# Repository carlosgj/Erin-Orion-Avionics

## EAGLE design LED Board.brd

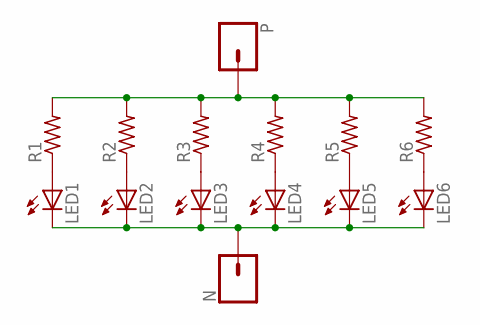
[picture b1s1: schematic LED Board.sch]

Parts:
LED1, LED2, LED3, LED4, LED5, LED6: LEDCHIPLED_1206; CHIPLED_1206
N: CONN_01; 1X01
P: CONN_01; 1X01
R1, R2, R3, R4, R5, R6: R-US_M1206; M1206

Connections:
unnamed: LED1.A, R1.1
unnamed: LED2.A, R2.1
unnamed: LED3.A, R3.1
unnamed: LED4.A, R4.1
unnamed: LED5.A, R5.1
unnamed: LED6.A, R6.1
unnamed: P.1, R1.2, R2.2, R3.2, R4.2, R5.2, R6.2
unnamed: LED1.C, LED2.C, LED3.C, LED4.C, LED5.C, LED6.C, N.1

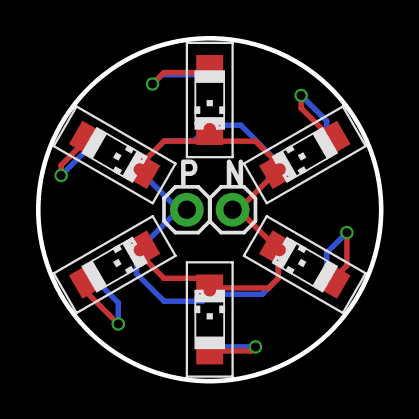
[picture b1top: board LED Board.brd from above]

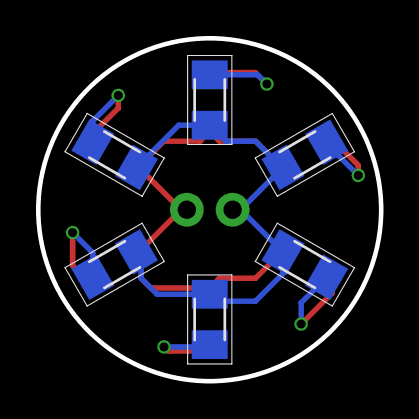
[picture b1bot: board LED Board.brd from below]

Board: 2 copper layers, 19.1 x 19.1 mm, 14 parts (6 on the bottom side), 8 nets.

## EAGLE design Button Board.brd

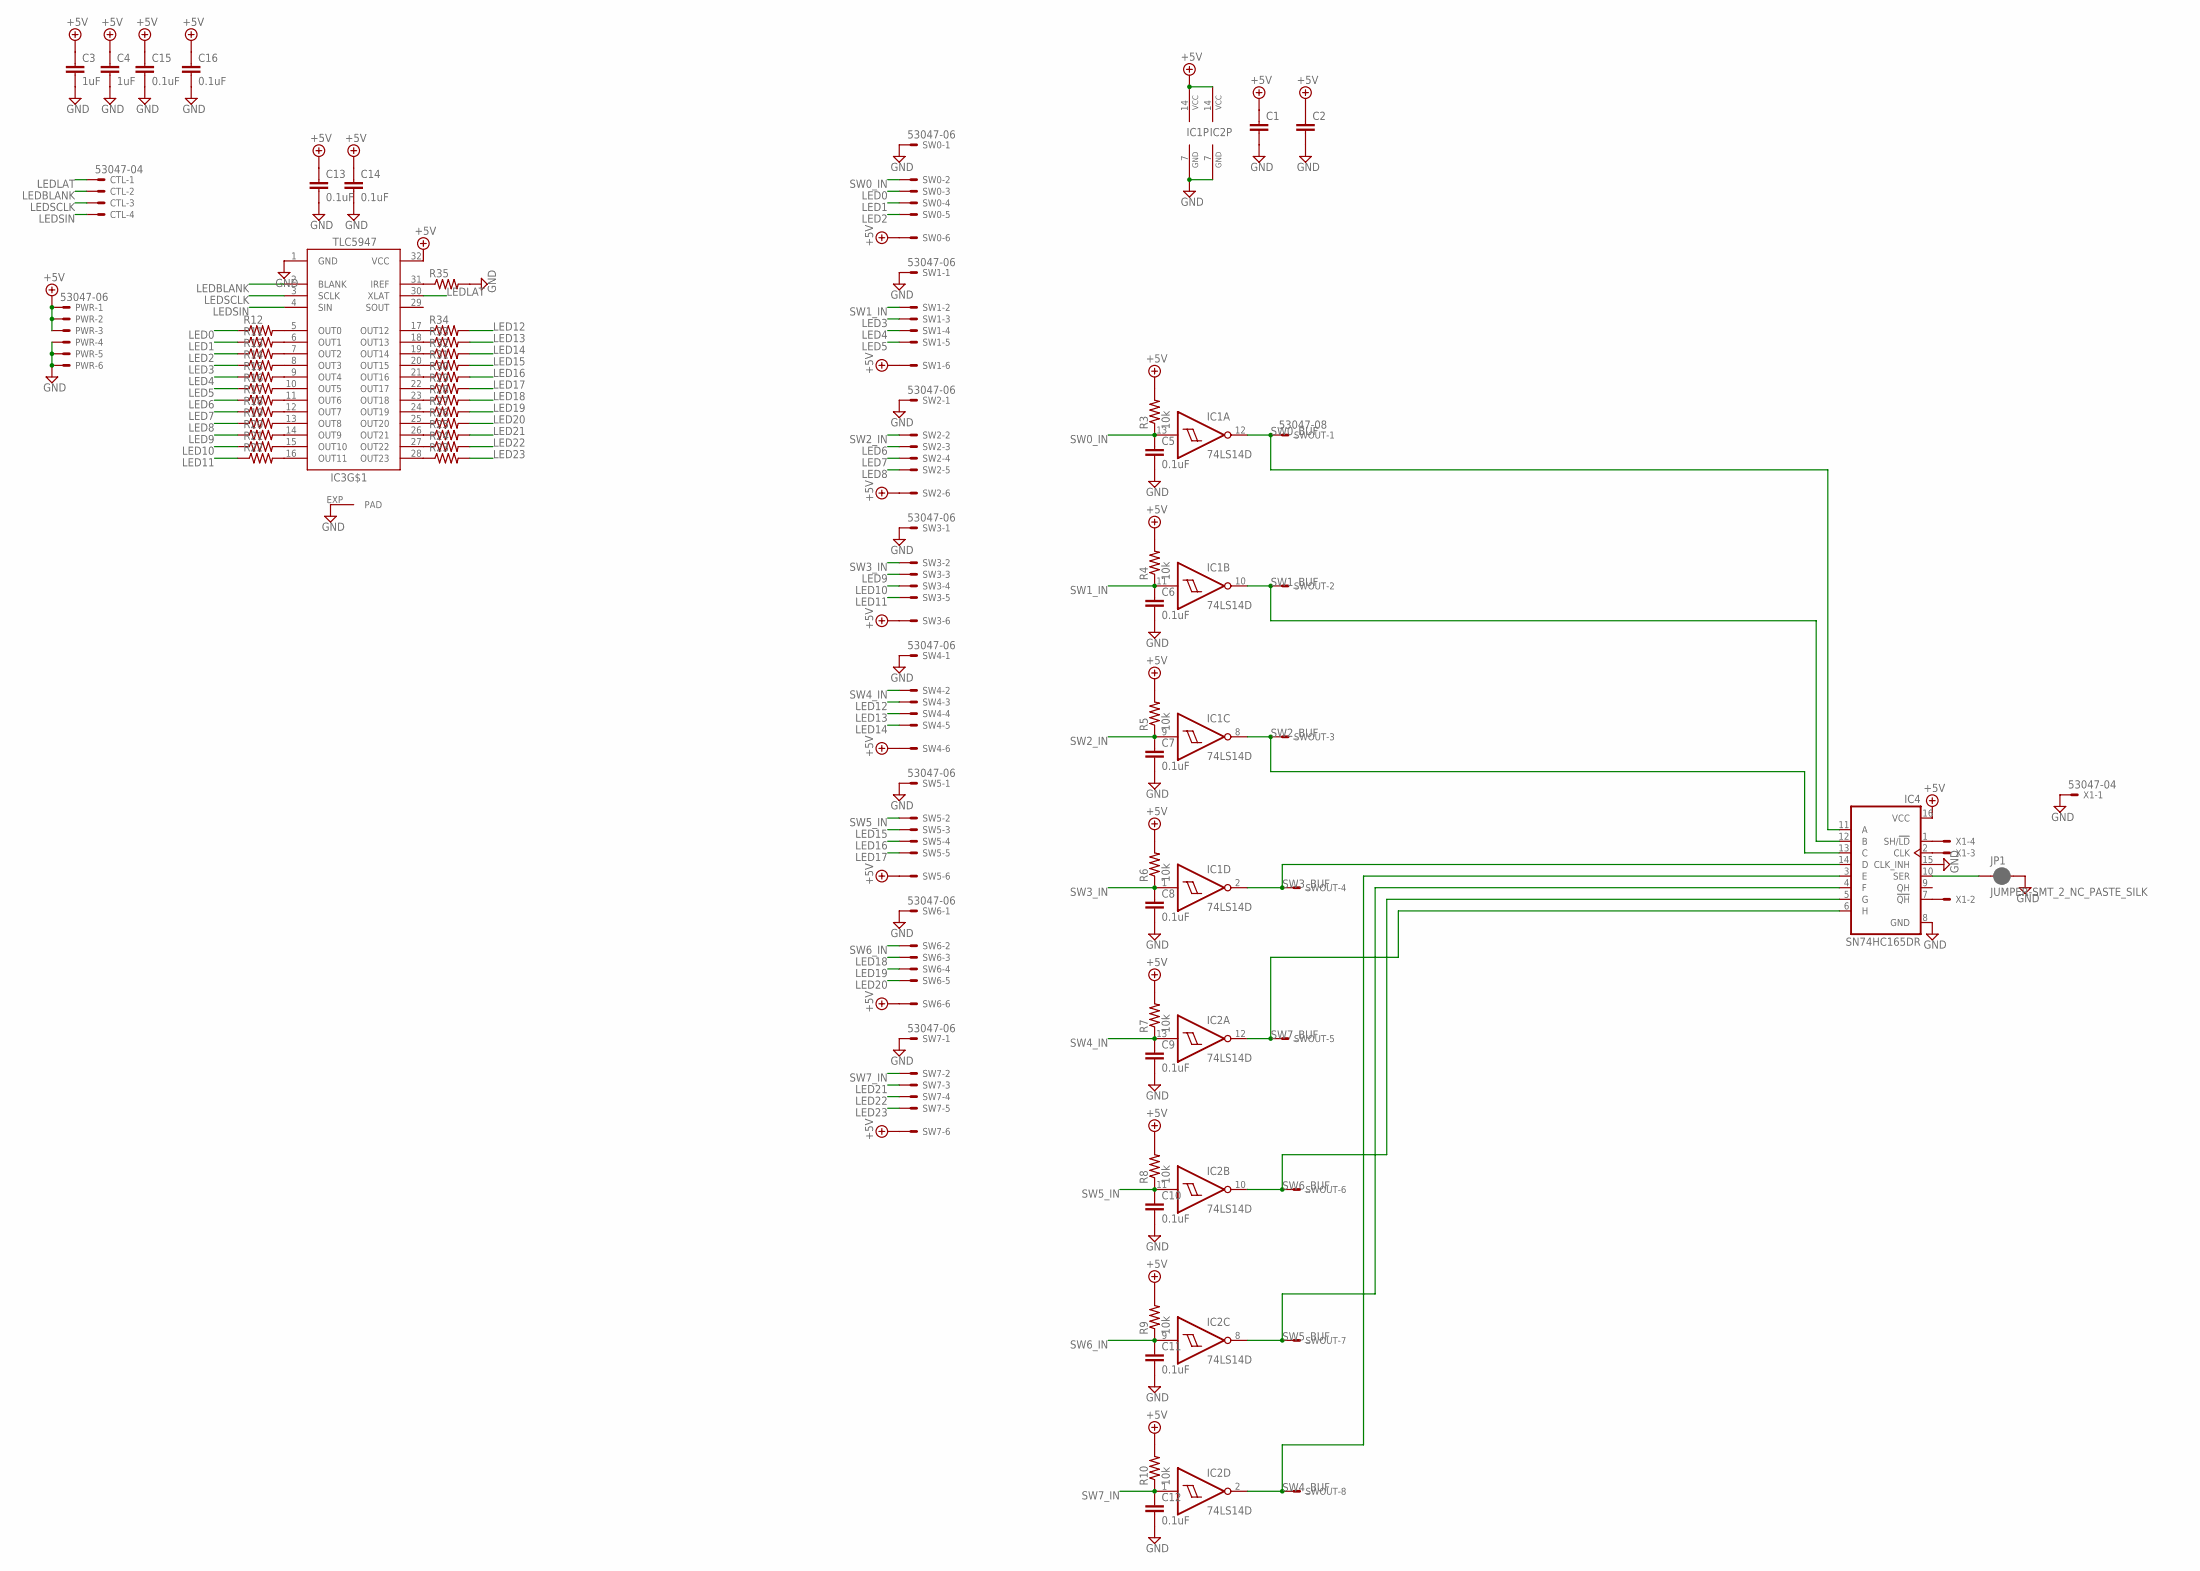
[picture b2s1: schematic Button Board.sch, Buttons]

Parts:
C1, C2: C-EUC1206; C1206
C3, C4: 1uF; C1206K
C5, C6, C7, C8, C9, C10, C11, C12, C13, C14: 0.1uF; C1206
C15, C16: 0.1uF; C1206K
CTL: 53047-04
IC1, IC2: 74LS14D; SO14
IC3: TLC5947-DAP; HTSSOP32DAP
IC4: SN74HC165DR; SO16
JP1: JUMPER-SMT_2_NC_PASTE_SILK; SMT-JUMPER_2_NC_PASTE_SILK
PWR: 53047-06
R3, R4, R5, R6, R7, R8, R9, R10: 10k; M1206
R11, R12, R13, R14, R15, R16, R17, R18, R19, R20, R21, R22, R23, R24, R25, R26, R27, R28, R29, R30, R31, R32, R33, R34, R35: R-US_M1206; M1206
SW0, SW1, SW2, SW3, SW4, SW5, SW6, SW7: 53047-06
SWOUT: 53047-08
X1: 53047-04

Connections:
+5V: C1.1, C2.1, C3.1, C4.1, C13.1, C14.1, C15.1, C16.1, IC1.14 (VCC), IC2.14 (VCC), IC3.32 (VCC), IC4.16 (VCC), PWR.1, PWR.2, PWR.3, R3.2, R4.2, R5.2, R6.2, R7.2, R8.2, R9.2, R10.2, SW0.6, SW1.6, SW2.6, SW3.6, SW4.6, SW5.6, SW6.6, SW7.6
GND: C1.2, C2.2, C3.2, C4.2, C5.2, C6.2, C7.2, C8.2, C9.2, C10.2, C11.2, C12.2, C13.2, C14.2, C15.2, C16.2, IC1.7 (GND), IC2.7 (GND), IC3.1 (GND), IC3.EXP (PAD), IC4.8 (GND), IC4.15 (CLK_INH), JP1.2, PWR.4, PWR.5, PWR.6, R35.2, SW0.1, SW1.1, SW2.1, SW3.1, SW4.1, SW5.1, SW6.1, SW7.1, X1.1
LED0: R12.1, SW0.3
LED1: R11.1, SW0.4
LED2: R13.1, SW0.5
LED3: R14.1, SW1.3
LED4: R15.1, SW1.4
LED5: R16.1, SW1.5
LED6: R17.1, SW2.3
LED7: R18.1, SW2.4
LED8: R19.1, SW2.5
LED9: R20.1, SW3.3
LED10: R21.1, SW3.4
LED11: R22.1, SW3.5
LED12: R34.2, SW4.3
LED13: R33.2, SW4.4
LED14: R32.2, SW4.5
LED15: R31.2, SW5.3
LED16: R30.2, SW5.4
LED17: R29.2, SW5.5
LED18: R28.2, SW6.3
LED19: R27.2, SW6.4
LED20: R26.2, SW6.5
LED21: R25.2, SW7.3
LED22: R24.2, SW7.4
LED23: R23.2, SW7.5
LEDBLANK: CTL.2, IC3.2 (BLANK)
LEDLAT: CTL.1, IC3.30 (XLAT)
LEDSCLK: CTL.3, IC3.3 (SCLK)
LEDSIN: CTL.4, IC3.4 (SIN)
unnamed: IC4.1 (SH/!LD), X1.4
unnamed: IC4.2 (CLK), X1.3
unnamed: IC3.5 (OUT0), R12.2
unnamed: IC3.6 (OUT1), R11.2
unnamed: IC3.7 (OUT2), R13.2
unnamed: IC3.8 (OUT3), R14.2
unnamed: IC3.9 (OUT4), R15.2
unnamed: IC3.11 (OUT6), R17.2
unnamed: IC3.12 (OUT7), R18.2
unnamed: IC3.13 (OUT8), R19.2
unnamed: IC3.15 (OUT10), R21.2
unnamed: IC3.16 (OUT11), R22.2
unnamed: IC3.28 (OUT23), R23.1
unnamed: IC3.27 (OUT22), R24.1
unnamed: IC3.26 (OUT21), R25.1
unnamed: IC3.25 (OUT20), R26.1
unnamed: IC3.24 (OUT19), R27.1
unnamed: IC3.23 (OUT18), R28.1
unnamed: IC3.22 (OUT17), R29.1
unnamed: IC3.21 (OUT16), R30.1
unnamed: IC3.20 (OUT15), R31.1
unnamed: IC3.19 (OUT14), R32.1
unnamed: IC3.18 (OUT13), R33.1
unnamed: IC3.17 (OUT12), R34.1
unnamed: IC3.10 (OUT5), R16.2
unnamed: IC3.14 (OUT9), R20.2
unnamed: IC3.31 (IREF), R35.1
unnamed: IC4.7 (!QH), X1.2
unnamed: IC4.10 (SER), JP1.1
SW0_BUF: IC1.12 (O), IC4.11 (A), SWOUT.1
SW0_IN: C5.1, IC1.13 (I), R3.1, SW0.2
SW1_BUF: IC1.10 (O), IC4.12 (B), SWOUT.2
SW1_IN: C6.1, IC1.11 (I), R4.1, SW1.2
SW2_BUF: IC1.8 (O), IC4.13 (C), SWOUT.3
SW2_IN: C7.1, IC1.9 (I), R5.1, SW2.2
SW3_BUF: IC1.2 (O), IC4.14 (D), SWOUT.4
SW3_IN: C8.1, IC1.1 (I), R6.1, SW3.2
SW4_BUF: IC2.2 (O), IC4.3 (E), SWOUT.8
SW4_IN: C9.1, IC2.13 (I), R7.1, SW4.2
SW5_BUF: IC2.8 (O), IC4.4 (F), SWOUT.7
SW5_IN: C10.1, IC2.11 (I), R8.1, SW5.2
SW6_BUF: IC2.10 (O), IC4.5 (G), SWOUT.6
SW6_IN: C11.1, IC2.9 (I), R9.1, SW6.2
SW7_BUF: IC2.12 (O), IC4.6 (H), SWOUT.5
SW7_IN: C12.1, IC2.1 (I), R10.1, SW7.2

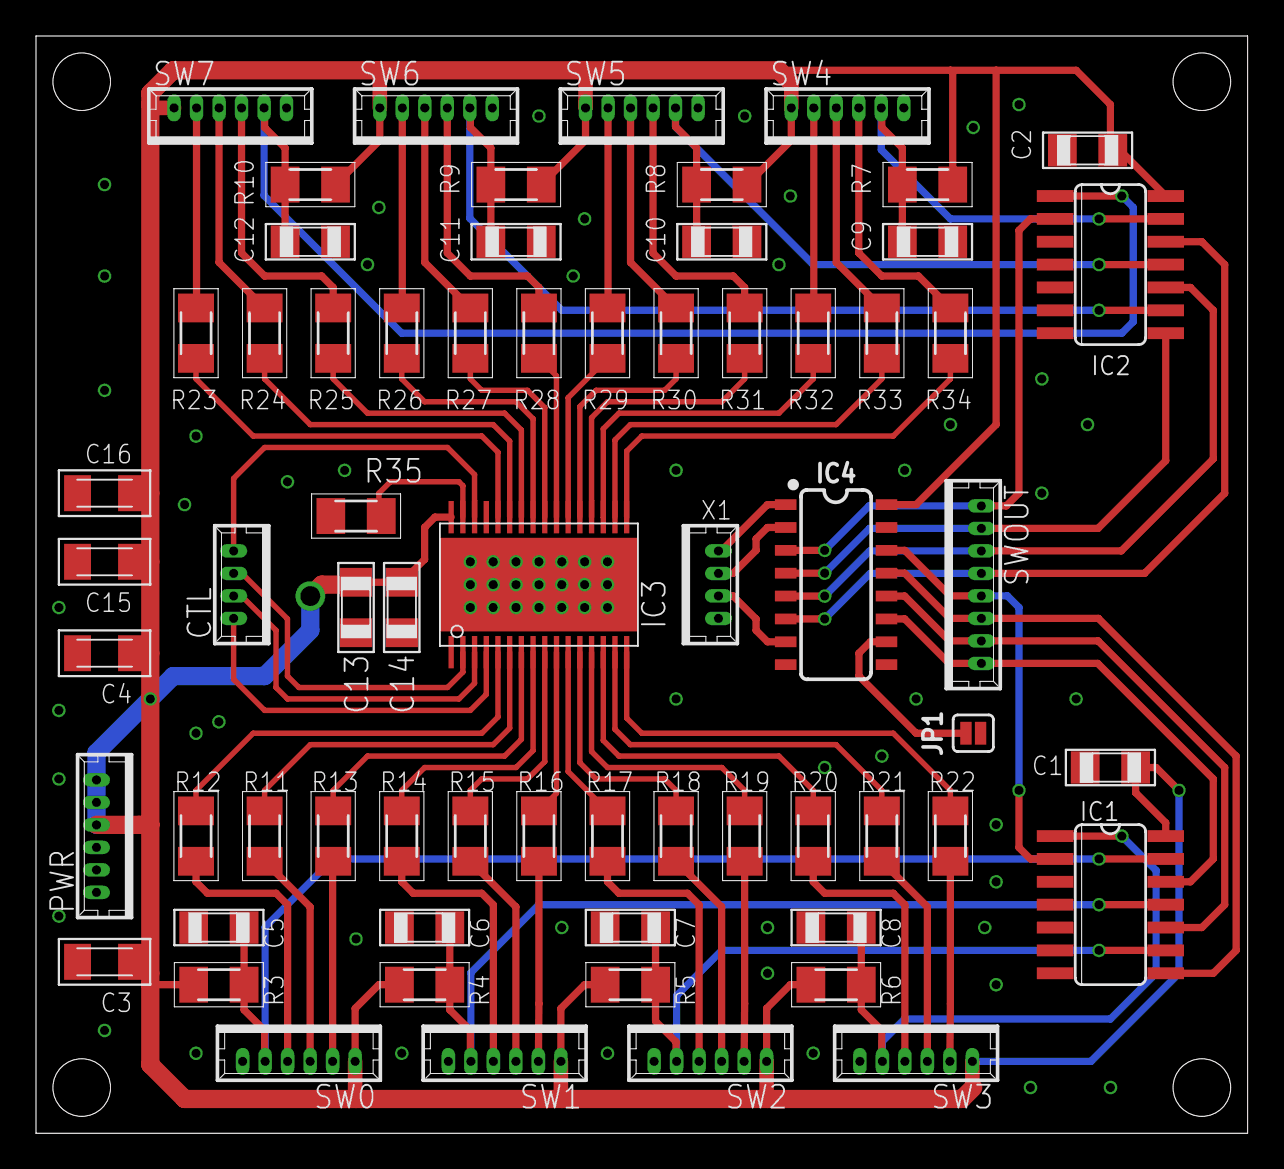
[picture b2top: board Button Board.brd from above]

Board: 2 copper layers, 67.3 x 61.0 mm, 66 parts (0 on the bottom side), 75 nets.

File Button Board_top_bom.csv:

Comment,Designator,Footprint,LCSC Part #
0,R11 R12 R13 R14 R15 R16 R17 R18 R19 R20 R21 R22 R23 R24 R25 R26 R27 R28 R29 R30 R31 R32 R33 R34 R35,M1206,C17888
0.1uF,C1 C2 C5 C6 C7 C8 C9 C10 C11 C12 C13 C14 C15 C16,C1206,C82601
1uF,C3 C4,C1206K,C1848
10k,R3 R4 R5 R6 R7 R8 R9 R10,M1206,C17902
74LS14D,IC1 IC2,SO14,C7653
SN74HC165DR,IC4,SO16,C5613

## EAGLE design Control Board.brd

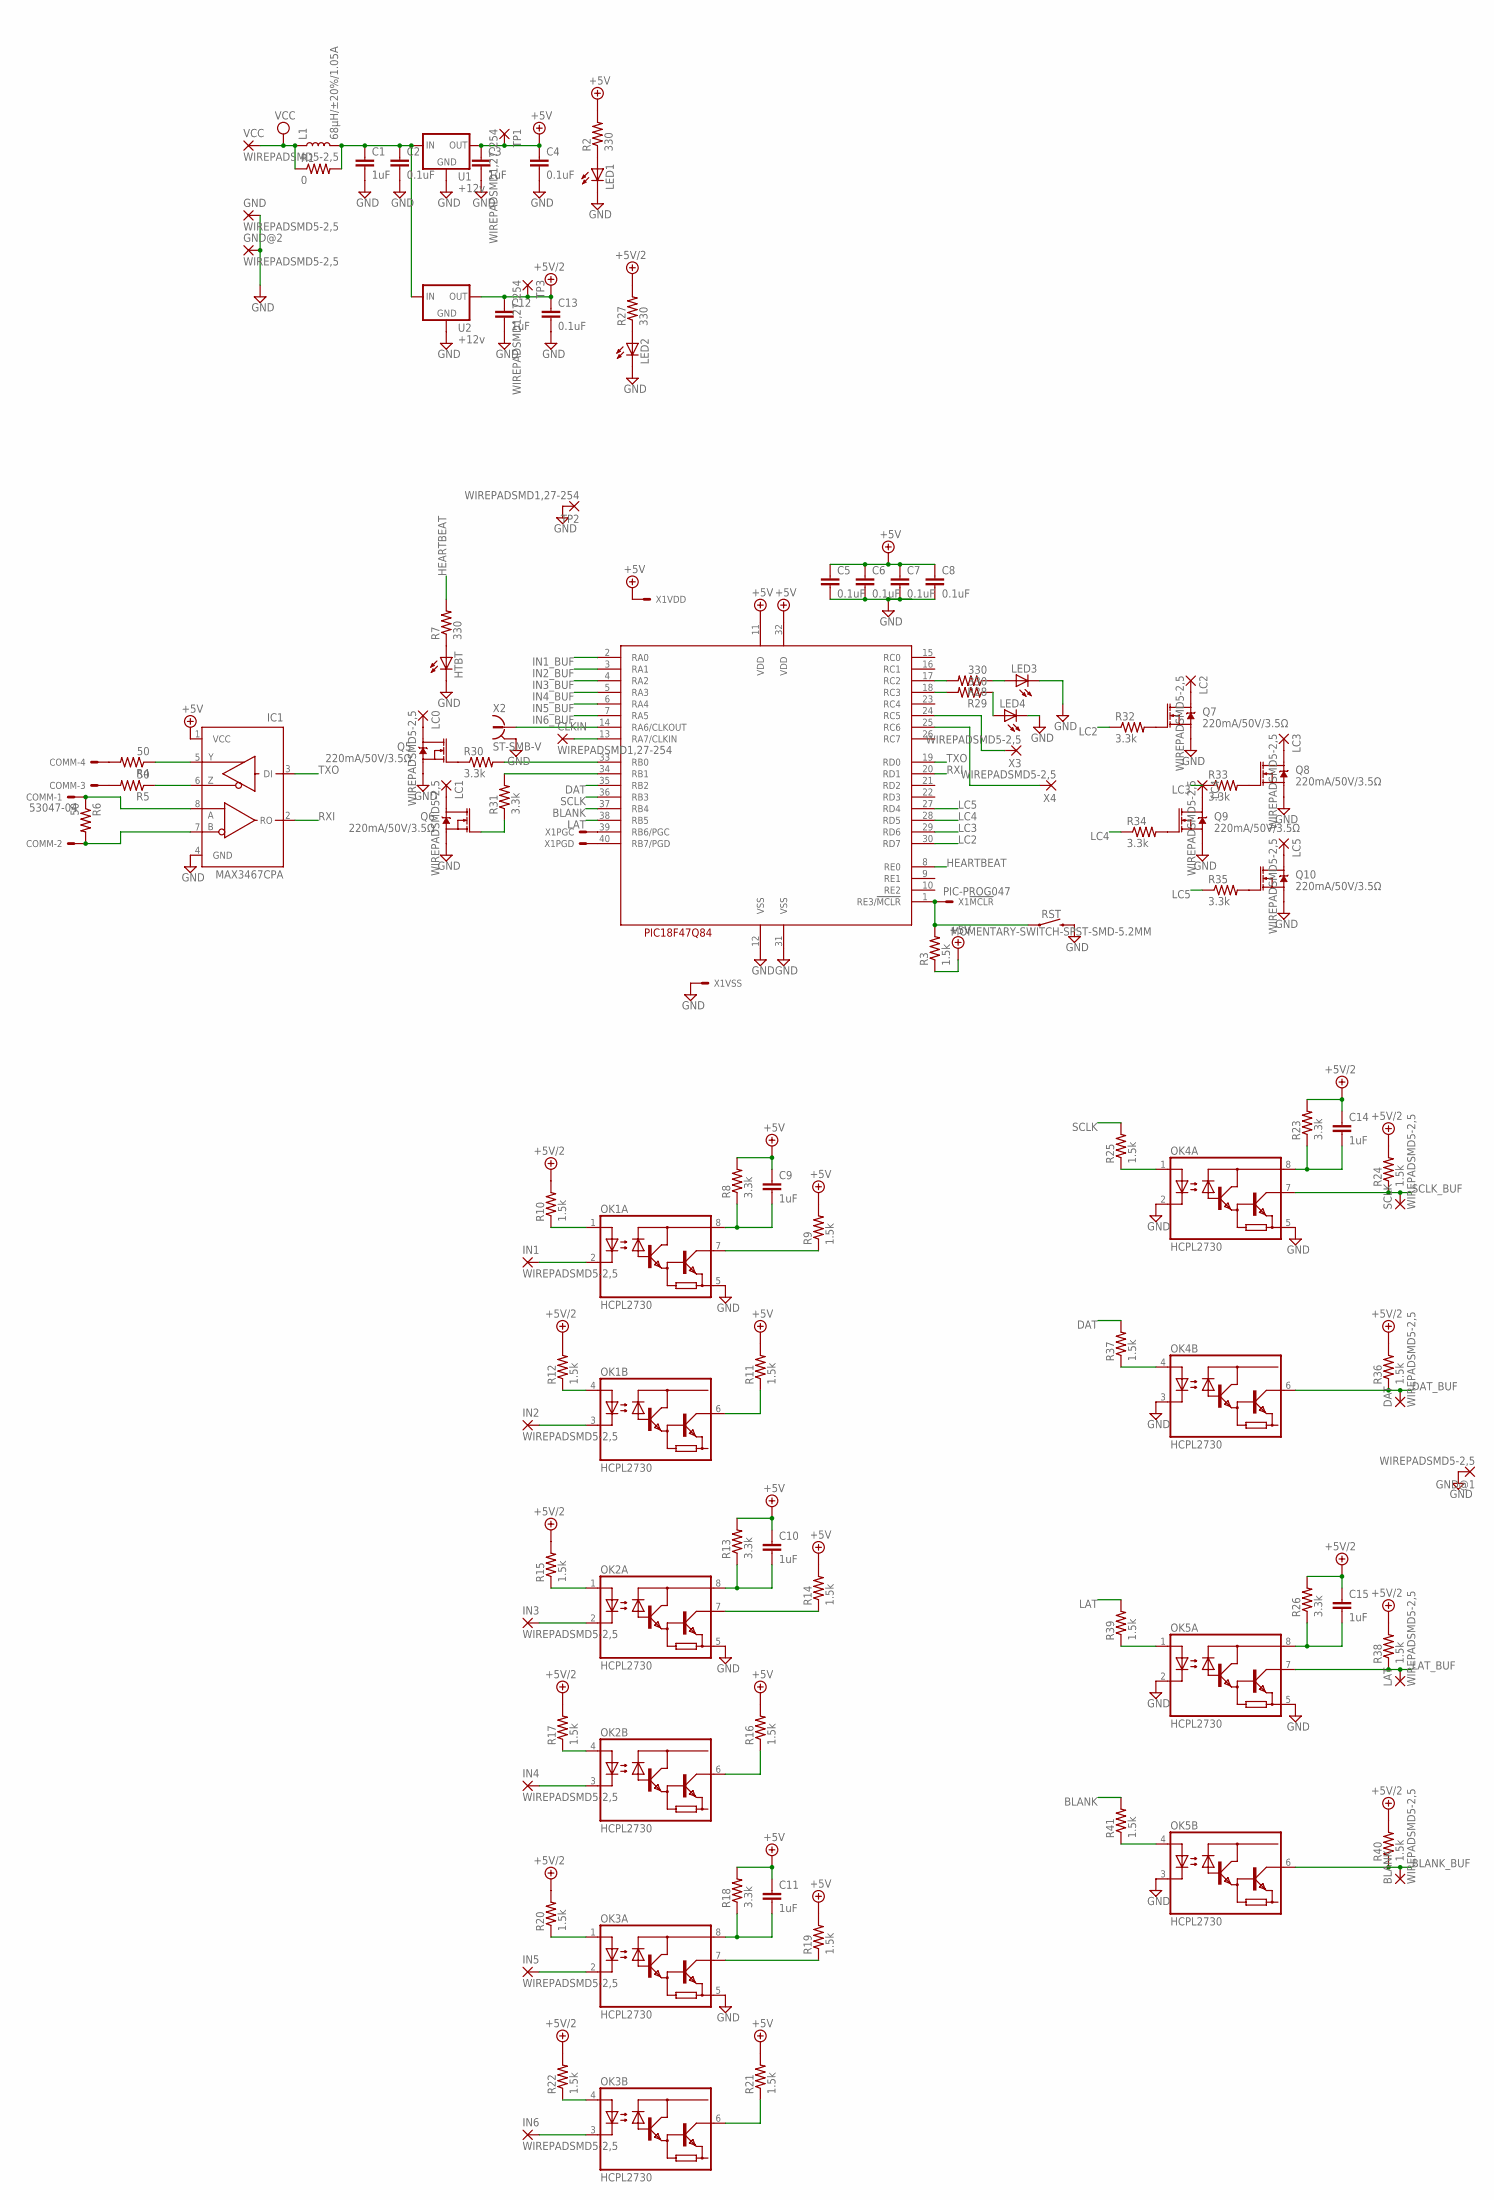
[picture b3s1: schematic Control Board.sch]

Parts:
BLANK: WIREPADSMD5-2,5; 5-2,5
C1, C3, C9, C10, C11, C12, C14, C15: 1uF; C1206
C2, C4, C5, C6, C7, C8, C13: 0.1uF; C1206
CLKIN: WIREPADSMD1,27-254; SMD1,27-2,54
COMM: 53047-04
DAT: WIREPADSMD5-2,5; 5-2,5
GND: WIREPADSMD5-2,5; 5-2,5
GND@1, GND@2: WIREPADSMD5-2,5; 5-2,5
HTBT: LEDCHIPLED_1206; CHIPLED_1206
IC1: MAX3467CPA; SO08
IN1, IN2, IN3, IN4, IN5, IN6: WIREPADSMD5-2,5; 5-2,5
L1: 68µH/±20%/1.05A; CR75
LAT: WIREPADSMD5-2,5; 5-2,5
LC0, LC1, LC2, LC3, LC4, LC5: WIREPADSMD5-2,5; 5-2,5
LED1, LED2, LED3, LED4: LEDCHIPLED_1206; CHIPLED_1206
OK1, OK2, OK3, OK4, OK5: HCPL2730; DIL08
Q5, Q6, Q7, Q8, Q9, Q10: 220mA/50V/3.5Ω; SOT23-3
R1: 0; M1206
R2, R7, R27, R28, R29: 330; M1206
R3, R9, R10, R11, R12, R14, R15, R16, R17, R19, R20, R21, R22, R24, R25, R36, R37, R38, R39, R40, R41: 1.5k; M1206
R4, R5, R6: 50; M1206
R8, R13, R18, R23, R26, R30, R31, R32, R33, R34, R35: 3.3k; M1206
RST: MOMENTARY-SWITCH-SPST-SMD-5.2MM; TACTILE_SWITCH_SMD_5.2MM
SCLK: WIREPADSMD5-2,5; 5-2,5
TP1, TP2, TP3: WIREPADSMD1,27-254; SMD1,27-2,54
U1, U2: +12v; TO-252
U$1: PIC18F47Q84; DIL40
VCC: WIREPADSMD5-2,5; 5-2,5
X1: PIC-PROG047; 53047-05
X2: ST-SMB-V
X3, X4: WIREPADSMD5-2,5; 5-2,5

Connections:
+5V: C3.1, C4.1, C5.1, C6.1, C7.1, C8.1, C9.1, C10.1, C11.1, IC1.1 (VCC), R2.2, R3.1, R8.2, R9.2, R11.2, R13.2, R14.2, R16.2, R18.2, R19.2, R21.2, TP1.1, U1.2 (OUT), U$1.11 (VDD), U$1.32 (VDD), X1.2
+5V/2: C12.1, C13.1, C14.1, C15.1, R10.2, R12.2, R15.2, R17.2, R20.2, R22.2, R23.2, R24.2, R26.2, R27.2, R36.2, R38.2, R40.2, TP3.1, U2.2 (OUT)
BLANK: R41.2, U$1.37 (RB4)
BLANK_BUF: BLANK.1, OK5.6 (VO2), R40.1
DAT: R37.2, U$1.35 (RB2)
DAT_BUF: DAT.1, OK4.6 (VO2), R36.1
GND: C1.2, C2.2, C3.2, C4.2, C5.2, C6.2, C7.2, C8.2, C12.2, C13.2, GND.1, GND@1.1, GND@2.1, HTBT.C, IC1.4 (GND), LED1.C, LED2.C, LED3.C, LED4.C, OK1.5 (GND), OK2.5 (GND), OK3.5 (GND), OK4.2 (C1), OK4.3 (C2), OK4.5 (GND), OK5.2 (C1), OK5.3 (C2), OK5.5 (GND), Q5.2 (S), Q6.2 (S), Q7.2 (S), Q8.2 (S), Q9.2 (S), Q10.2 (S), RST.3 (2), TP2.1, U1.3 (GND), U2.3 (GND), U$1.12 (VSS), U$1.31 (VSS), X1.3, X2.2, X2.3 (2), X2.4 (2), X2.5 (2)
HEARTBEAT: R7.2, U$1.8 (RE0)
IN1: IN1.1, OK1.2 (C1)
IN1_BUF: OK1.7 (VO1), R9.1, U$1.2 (RA0)
IN2: IN2.1, OK1.3 (C2)
IN2_BUF: OK1.6 (VO2), R11.1, U$1.3 (RA1)
IN3: IN3.1, OK2.2 (C1)
IN3_BUF: OK2.7 (VO1), R14.1, U$1.4 (RA2)
IN4: IN4.1, OK2.3 (C2)
IN4_BUF: OK2.6 (VO2), R16.1, U$1.5 (RA3)
IN5: IN5.1, OK3.2 (C1)
IN5_BUF: OK3.7 (VO1), R19.1, U$1.6 (RA4)
IN6: IN6.1, OK3.3 (C2)
IN6_BUF: OK3.6 (VO2), R21.1, U$1.7 (RA5)
LAT: R39.2, U$1.38 (RB5)
LAT_BUF: LAT.1, OK5.7 (VO1), R38.1
LC2: R32.1, U$1.30 (RD7)
LC3: R33.1, U$1.29 (RD6)
LC4: R34.1, U$1.28 (RD5)
LC5: R35.1, U$1.27 (RD4)
unnamed: C1.1, C2.1, L1.P$2 (2), R1.2, U1.1 (IN), U2.1 (IN)
unnamed: LED1.A, R2.1
unnamed: R3.2, RST.1, U$1.1 (RE3/!MCLR), X1.1
unnamed: U$1.40 (RB7/PGD), X1.4
unnamed: U$1.39 (RB6/PGC), X1.5
unnamed: U$1.14 (RA6/CLKOUT), X2.1
unnamed: IC1.5 (Y), R4.1
unnamed: IC1.6 (Z), R5.1
unnamed: COMM.1, IC1.8 (A), R6.1
unnamed: COMM.2, IC1.7 (B), R6.2
unnamed: COMM.4, R4.2
unnamed: COMM.3, R5.2
unnamed: HTBT.A, R7.1
unnamed: CLKIN.1, U$1.13 (RA7/CLKIN)
unnamed: C9.2, OK1.8 (VCC), R8.1
unnamed: C10.2, OK2.8 (VCC), R13.1
unnamed: OK2.1 (A1), R15.1
unnamed: OK1.1 (A1), R10.1
unnamed: OK2.4 (A2), R17.1
unnamed: OK1.4 (A2), R12.1
unnamed: C11.2, OK3.8 (VCC), R18.1
unnamed: OK3.1 (A1), R20.1
unnamed: OK3.4 (A2), R22.1
unnamed: C14.2, OK4.8 (VCC), R23.1
unnamed: OK4.1 (A1), R25.1
unnamed: C15.2, OK5.8 (VCC), R26.1
unnamed: OK4.4 (A2), R37.1
unnamed: OK5.1 (A1), R39.1
unnamed: LED2.A, R27.1
unnamed: OK5.4 (A2), R41.1
unnamed: R28.2, U$1.17 (RC2)
unnamed: R29.2, U$1.18 (RC3)
unnamed: LED3.A, R28.1
unnamed: LED4.A, R29.1
unnamed: R30.2, U$1.33 (RB0)
unnamed: R31.2, U$1.34 (RB1)
unnamed: Q5.1 (G), R30.1
unnamed: Q6.1 (G), R31.1
unnamed: LC0.1, Q5.3 (D)
unnamed: LC1.1, Q6.3 (D)
unnamed: Q7.1 (G), R32.2
unnamed: Q8.1 (G), R33.2
unnamed: Q9.1 (G), R34.2
unnamed: Q10.1 (G), R35.2
unnamed: LC2.1, Q7.3 (D)
unnamed: LC3.1, Q8.3 (D)
unnamed: LC4.1, Q9.3 (D)
unnamed: LC5.1, Q10.3 (D)
unnamed: U$1.25 (RC6), X4.1
unnamed: U$1.24 (RC5), X3.1
RXI: IC1.2 (RO), U$1.20 (RD1)
SCLK: R25.2, U$1.36 (RB3)
SCLK_BUF: OK4.7 (VO1), R24.1, SCLK.1
TXO: IC1.3 (DI), U$1.19 (RD0)
VCC: L1.P$1 (1), R1.1, VCC.1

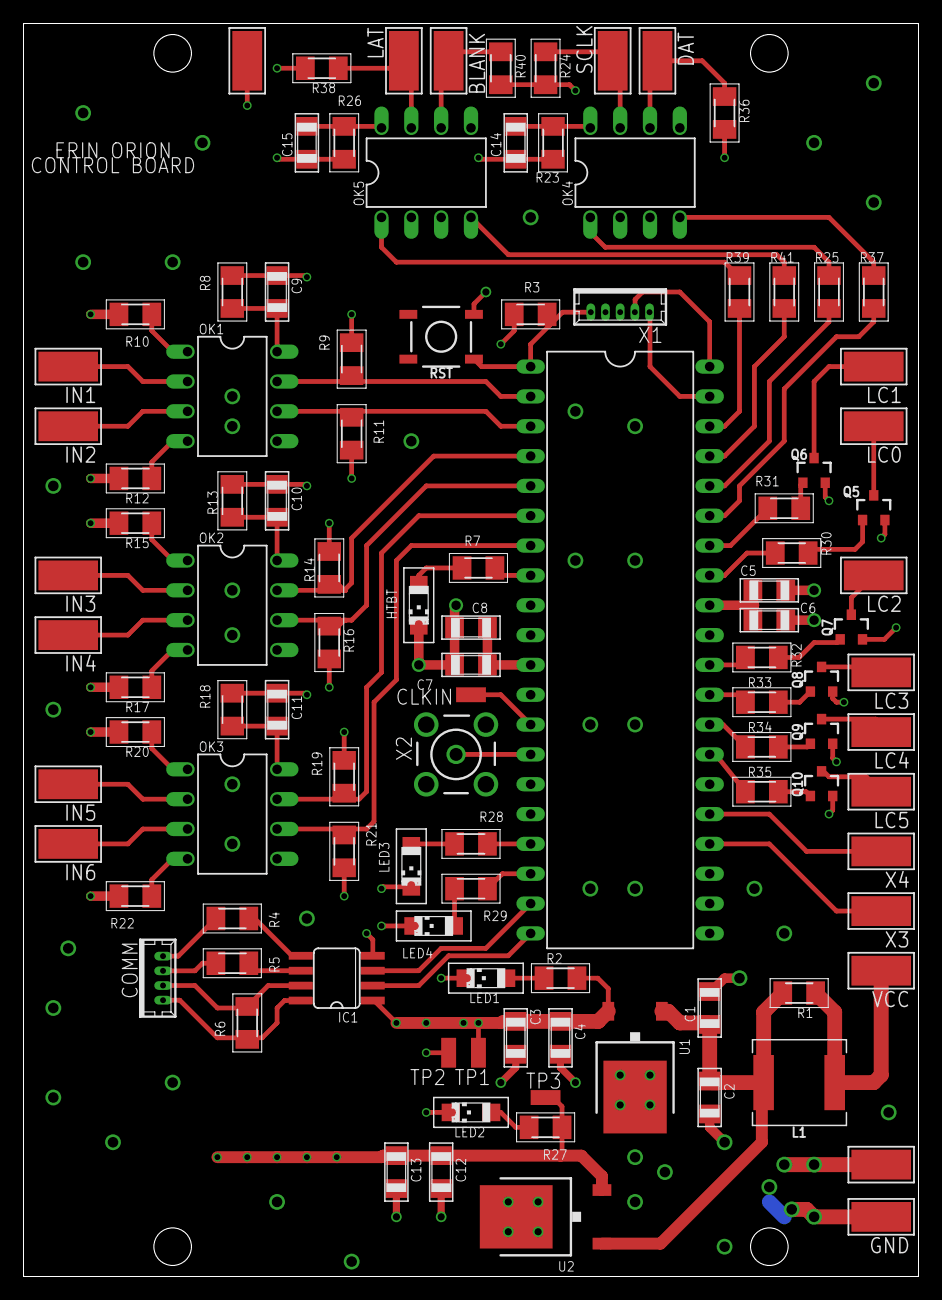
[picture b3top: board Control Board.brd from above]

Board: 4 copper layers, 76.2 x 106.7 mm, 107 parts (0 on the bottom side), 81 nets.

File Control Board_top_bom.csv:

Comment,Designator,Footprint,LCSC Part #
,HTBT LED1 LED2 LED3 LED4,CHIPLED_1206,C93133
+12v,U1 U2,TO-252,C58069
0.1uF,C2 C4 C5 C6 C7 C8 C13,C1206,C24497
1.5k,R3 R9 R10 R11 R12 R14 R15 R16 R17 R19 R20 R21 R22 R24 R25 R36 R37 R38 R39 R40 R41,M1206,C237775
1uF,C1 C3 C9 C10 C11 C12 C14 C15,C1206,C1848
3.3k,R8 R13 R18 R23 R26 R30 R31 R32 R33 R34 R35,M1206,C26032
220mA/50V/3.5O,Q5 Q6 Q7 Q8 Q9 Q10,SOT23-3,C2938375
330,R2 R7 R27 R28 R29,M1206,C114944

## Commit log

2023-03-30 Board designs
2023-04-02 Lots of work, mostly params and PRNG
2023-04-02 Fixing param set
2023-04-05 Fixing PRNG params
2023-04-09 NeoPixel works!
2023-04-09 Misc
2023-04-09 LED Board
2023-04-09 Using temperature to add more randomness to PRNG
2023-04-09 Working on thruster/maneuver logic
2023-04-10 Lots of lighting business logic
2023-04-11 Working on thruster timing
2023-04-12 Final software (hopefully)!
2023-04-12 Disabling maneuver in night mode

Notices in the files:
parts and their libraries:
SparkFun-IC-Logic: Licensing: Creative Commons ShareAlike 4.0 International - https://creativecommons.org/licenses/by-sa/4.0
